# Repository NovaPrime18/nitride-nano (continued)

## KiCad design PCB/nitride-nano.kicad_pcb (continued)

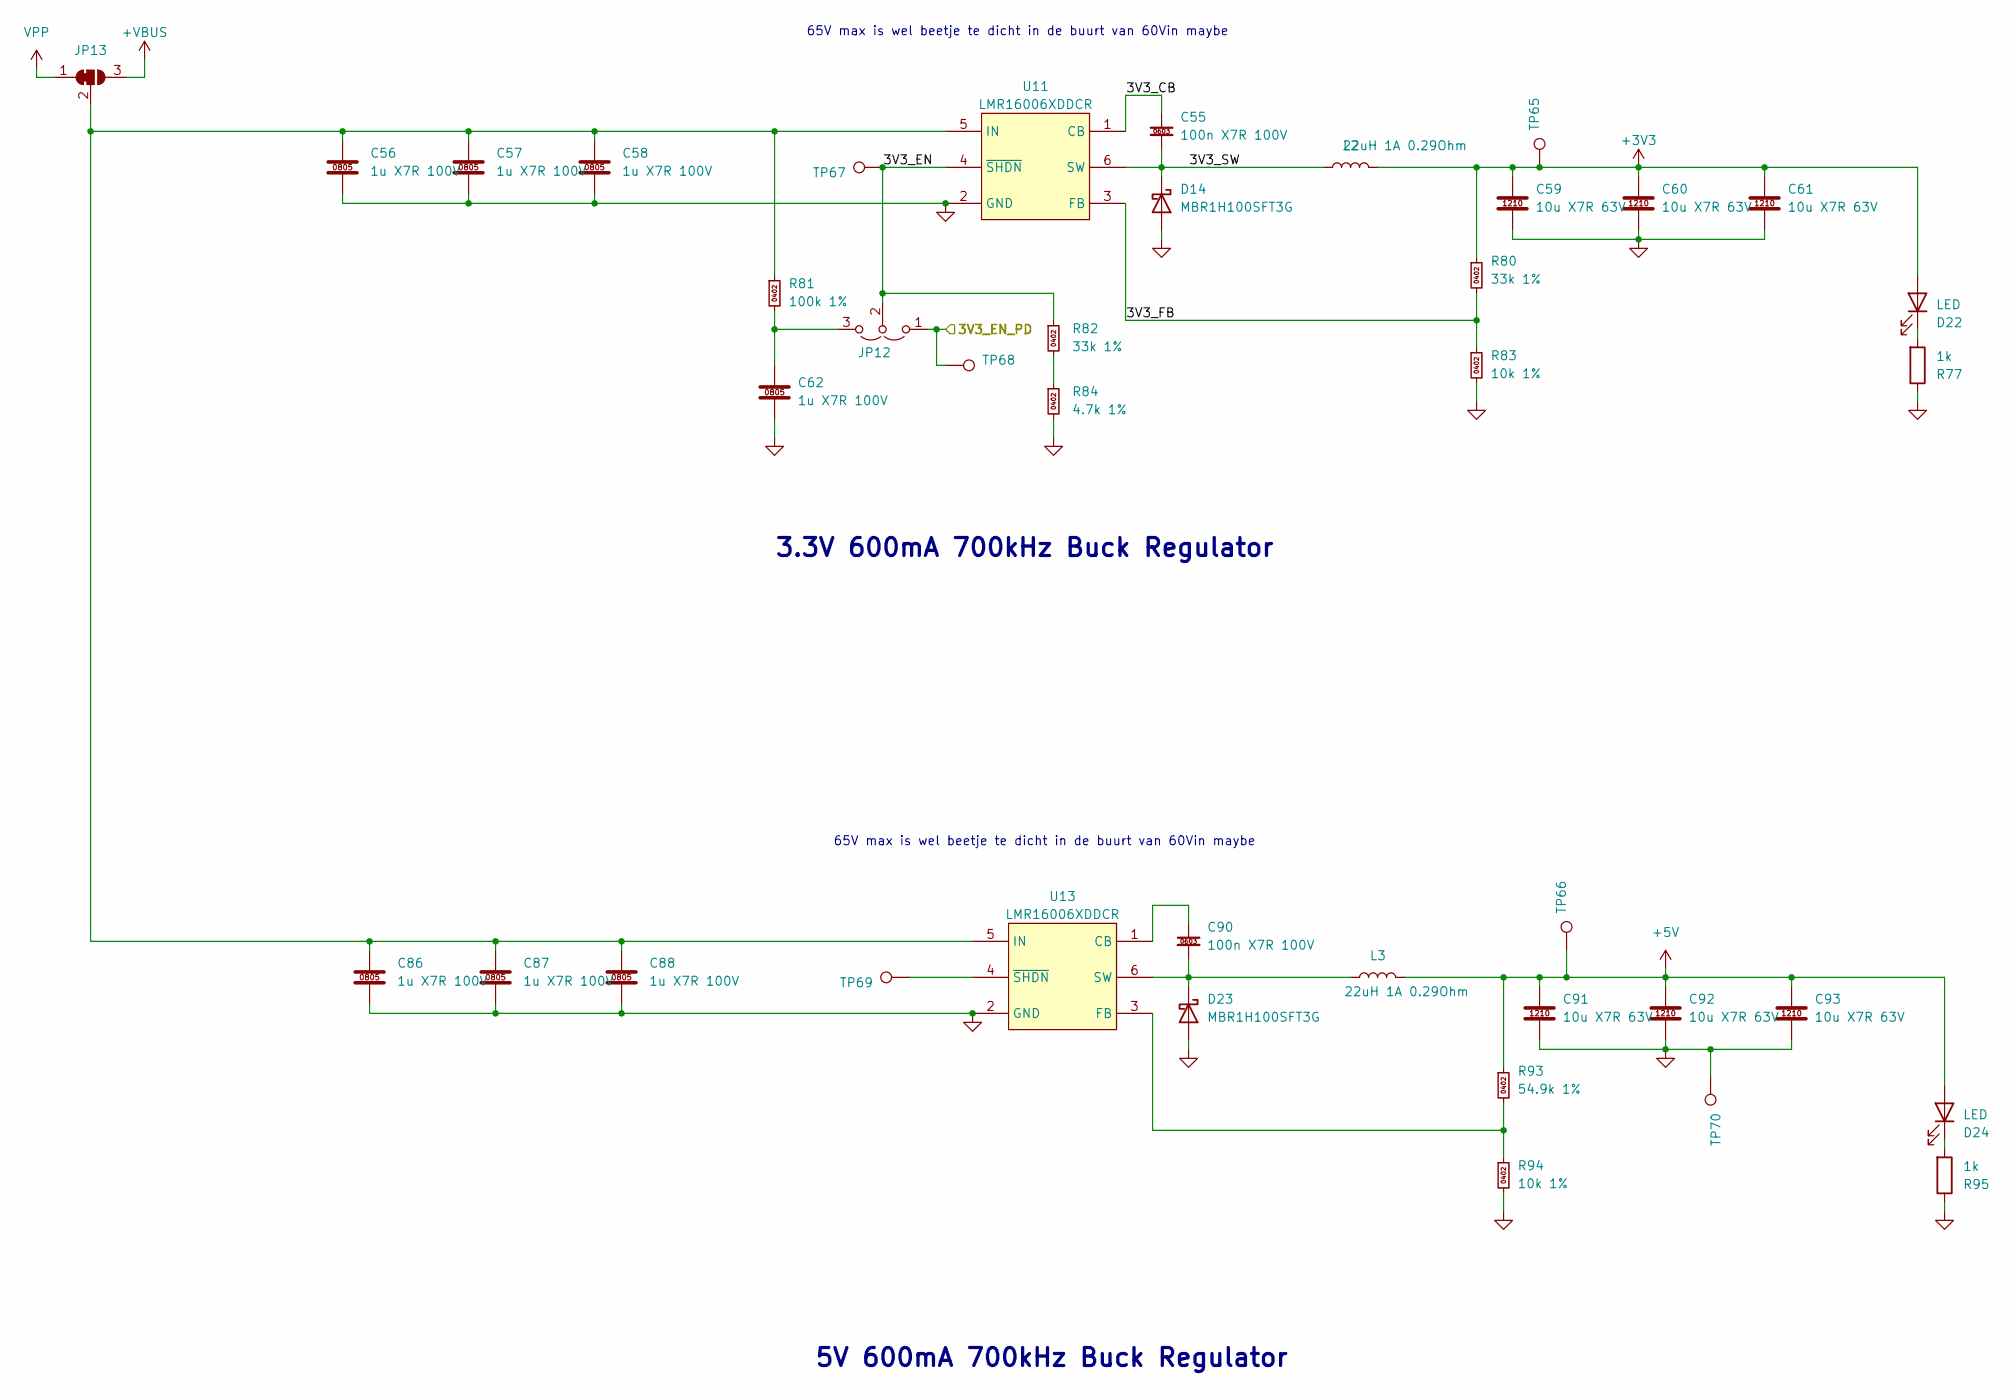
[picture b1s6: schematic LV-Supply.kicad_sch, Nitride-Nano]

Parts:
C55, C90: 100n X7R 100V; C_0603_1608Metric; Manufacturer Part Number CL10B104KC8NNNC; LCSC C15725
C56, C57, C58, C62, C86, C87, C88: 1u X7R 100V; C_0805_2012Metric; Manufacturer Part Number CC0805KKX7R0BB105; LCSC C5370002
C59, C60, C61, C91, C92, C93: 10u X7R 63V; C_1210_3225Metric; Manufacturer Part Number GRM32ER71J106KA12L; LCSC C437568
D14, D23: MBR1H100SFT3G; sod-123fl_305p_260x160x90_n; Manufacturer Part Number MBR1H100SFT3G; LCSC C235757
D22, D24: LED; LED_0603_1608Metric
JP12: jumper_solder_3pad_no; jumper_solder_3pad_no_40x40_20
JP13: SolderJumper_3_Bridged12; SolderJumper-3_P1.3mm_Bridged12_RoundedPad1.0x1.5mm_NumberL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
L2, L3: 22uH 1A 0.29Ohm; SWPA4030S220MT; Manufacturer Part Number SWPA4030S220MT; LCSC C83472
R77, R95: 1k; R_0402_1005Metric
R80, R82: 33k 1%; R_0402_1005Metric; Manufacturer Part Number RC0402FR-0733KL; LCSC C138003
R81: 100k 1%; R_0402_1005Metric; Manufacturer Part Number 0402WGF1003TCE; LCSC C25741
R83, R94: 10k 1%; R_0402_1005Metric; Manufacturer Part Number 0402WGF1002TCE; LCSC C25744
R84: 4.7k 1%; R_0402_1005Metric; Manufacturer Part Number 0402WGF1003TCE; LCSC C25741
R93: 54.9k 1%; R_0402_1005Metric
TP65, TP66, TP67, TP68, TP69, TP70: tp_round_70; TestPoint_Pad_D1.0mm
U11, U13: LMR16006XDDCR; sot6_p95_290x180x110_n; Manufacturer Part Number LMR16006XDDCR; LCSC C87080

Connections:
+3V3: C59.1, C60.1, C61.1, D22.2 (A), L2.2, R80.1, TP65.1 (1_1); also elsewhere on the board
+5V: C91.1, C92.1, C93.1, D24.2 (A), L3.2, R93.1, TP66.1 (1_1); also elsewhere on the board
+VBUS: JP13.3 (B); also elsewhere on the board
/LV-Supply/3V3_CB: C55.1, U11.1 (CB)
/LV-Supply/3V3_EN: JP12.2 (C), R82.1, TP67.1 (1_1), U11.4 (~SHDN); also elsewhere on the board
/LV-Supply/3V3_EN_PD: JP12.1 (A), TP68.1 (1_1); also elsewhere on the board
/LV-Supply/3V3_SW: C55.2, D14.1 (K), L2.1, U11.6 (SW)
unnamed: D22.1 (K), R77.2
unnamed: C90.2, D23.1 (K), L3.1, U13.6 (SW)
unnamed: D24.1 (K), R95.2
unnamed: R82.2, R84.1
unnamed: C90.1, U13.1 (CB)
unnamed: TP69.1 (1_1), U13.4 (~SHDN)
VPP: JP13.1 (A); also elsewhere on the board

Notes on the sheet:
65V max is wel beetje te dicht in de buurt van 60Vin maybe
3.3V 600mA 700kHz Buck Regulator
5V 600mA 700kHz Buck Regulator

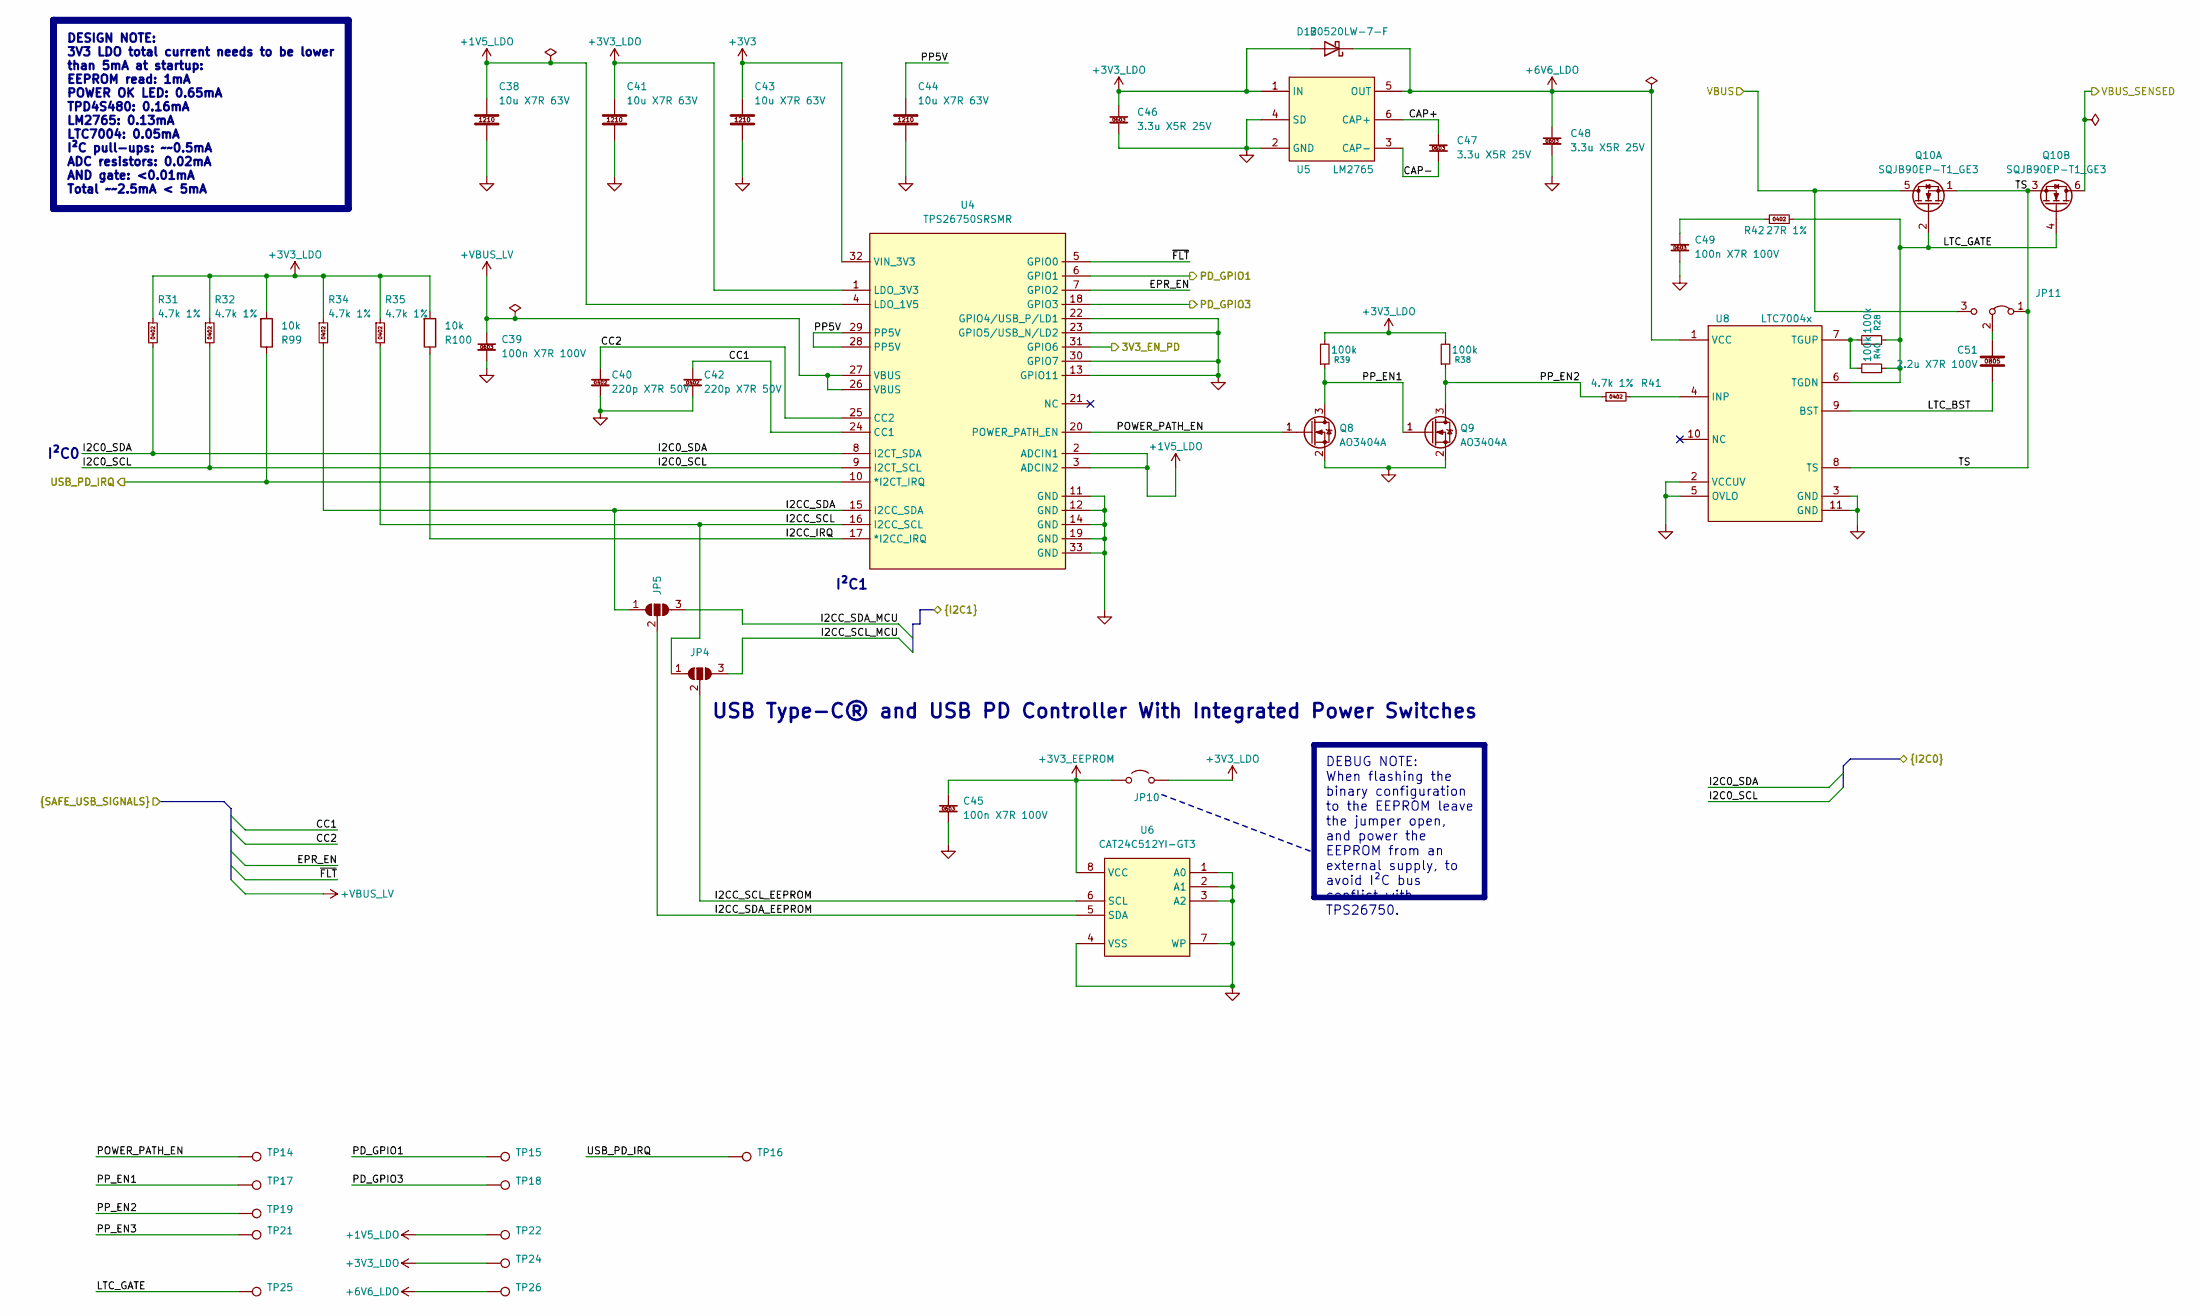
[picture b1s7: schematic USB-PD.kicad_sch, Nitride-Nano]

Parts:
C38, C41, C43, C44: 10u X7R 63V; C_1210_3225Metric; Manufacturer Part Number GRM32ER71J106KA12L; LCSC C437568
C39, C45, C49: 100n X7R 100V; C_0603_1608Metric; Manufacturer Part Number CL10B104KC8NNNC; LCSC C15725
C40, C42: 220p X7R 50V; C_0402_1005Metric; Manufacturer Part Number CL05B221KB5NNNC; LCSC C296710
C46, C47, C48: 3.3u X5R 25V; C_0603_1608Metric; Manufacturer Part Number TCC0603X5R335M250CT; LCSC C5360803
C51: 2.2u X7R 100V; C_0805_2012Metric; Manufacturer Part Number HHV0805R7225K101NSLJ; LCSC C22367838
D12: B0520LW-7-F; sod-123_270x155135_n; Manufacturer Part Number B0520LW-7-F; LCSC C155367
JP4, JP5: SolderJumper_3_Open; SolderJumper-3_P1.3mm_Open_RoundedPad1.0x1.5mm
JP10: jumper_solder_2pad_no_kicad; SolderJumper-2_P1.3mm_Open_RoundedPad1.0x1.5mm
JP11: jumper_solder_3pad_12nc_kicad; SolderJumper-3_P1.3mm_Bridged2Bar12_RoundedPad1.0x1.5mm
Q8, Q9: AO3404A; sot-23-3L_103p_300x130x110_n; Manufacturer Part Number AO3404A; LCSC C30010
Q10: SQJB90EP-T1_GE3; PowerPAKSO-8_127p_513x615x120_n; Manufacturer Part Number SQJB90EP-T1_GE3; LCSC C727731
R28, R38, R39, R40: 100k; R_0402_1005Metric; LCSC C60491
R31, R32, R34, R35, R41: 4.7k 1%; R_0402_1005Metric; Manufacturer Part Number 0402WGF1003TCE; LCSC C105871
R42: 27R 1%; R_0402_1005Metric; Manufacturer Part Number RC0402FR-0727RL; LCSC C138021
R99, R100: 10k; R_0402_1005Metric; LCSC C2906861
TP14, TP15, TP16, TP17, TP18, TP19, TP21, TP22, TP24, TP25, TP26: tp_round_70; TestPoint_Pad_D1.0mm
U4: TPS26750SRSMR; qfn32_40p_400x400x100_tp_280x280_mfg; Manufacturer Part Number TPS26750SRSMR; LCSC C42166327
U5: LM2765; sot236_p95_290x160x110_n; Manufacturer Part Number LM2765M6X/NOPB; LCSC C140270
U6: CAT24C512YI-GT3; JEDEC_MO-153_AA; Manufacturer Part Number CAT24C512YI-GT3; LCSC C56096
U8: LTC7004x; msop_10p_300x490x110_tp168x188_n; Manufacturer Part Number LTC7004EMSE#TRPBF; LCSC C690106

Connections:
+1V5_LDO: C38.1, TP22.1 (1_1), U4.2 (ADCIN1), U4.3 (ADCIN2), U4.4 (LDO_1V5)
+3V3: C43.1, U4.32 (VIN_3V3); also elsewhere on the board
+3V3_EEPROM: C45.1, JP10.1 (A), U6.8 (VCC)
+3V3_LDO: C41.1, C46.1, D12.2 (A), JP10.2 (B), R31.1, R32.1, R34.1, R35.1, R38.2, R39.2, R99.2, R100.2, TP24.1 (1_1), U4.1 (LDO_3V3), U5.1 (IN); also elsewhere on the board
+6V6_LDO: C48.1, D12.1 (K), TP26.1 (1_1), U5.5 (OUT), U8.1 (VCC)
+VBUS: JP11.3 (B), Q10.5 (D); also elsewhere on the board
+VBUS_LV: C39.1, U4.26 (VBUS), U4.27 (VBUS); also elsewhere on the board
/LV-Supply/3V3_EN_PD: U4.31 (GPIO6); also elsewhere on the board
/MCU/I2C0_SCL: R32.2, U4.9 (I2CT_SCL); also elsewhere on the board
/MCU/I2C0_SDA: R31.2, U4.8 (I2CT_SDA); also elsewhere on the board
/MCU/I2CC_SCL_MCU: JP4.3 (B); also elsewhere on the board
/MCU/I2CC_SDA_MCU: JP5.3 (B); also elsewhere on the board
/Power-Sense-In/+VBUS_SENSED: Q10.6 (D); also elsewhere on the board
/USB-PD/CAP+: C47.1, U5.6 (CAP+)
/USB-PD/CAP-: C47.2, U5.3 (CAP-)
/USB-PD/CC1: C42.1, U4.24 (CC1); also elsewhere on the board
/USB-PD/CC2: C40.1, U4.25 (CC2); also elsewhere on the board
/USB-PD/EPR_EN: U4.7 (GPIO2); also elsewhere on the board
/USB-PD/I2CC_IRQ: R100.1, U4.17 (*I2CC_IRQ)
/USB-PD/I2CC_SCL: JP4.1 (A), R35.2, U4.16 (I2CC_SCL)
/USB-PD/I2CC_SCL_EEPROM: JP4.2 (C), U6.6 (SCL)
/USB-PD/I2CC_SDA: JP5.1 (A), R34.2, U4.15 (I2CC_SDA)
/USB-PD/I2CC_SDA_EEPROM: JP5.2 (C), U6.5 (SDA)
/USB-PD/LTC_BST: C51.2, U8.9 (BST)
/USB-PD/LTC_GATE: Q10.2 (G), Q10.4 (G), R28.1, R40.1, R42.2, TP25.1 (1_1), U8.6 (TGDN)
/USB-PD/PD_GPIO1: TP15.1 (1_1), U4.6 (GPIO1); also elsewhere on the board
/USB-PD/PD_GPIO3: TP18.1 (1_1), U4.18 (GPIO3); also elsewhere on the board
/USB-PD/POWER_PATH_EN: Q8.1 (G), TP14.1 (1_1), U4.20 (POWER_PATH_EN)
/USB-PD/PP5V: C44.1, U4.28 (PP5V), U4.29 (PP5V)
/USB-PD/PP_EN1: Q8.3 (D), Q9.1 (G), R39.1, TP17.1 (1_1)
/USB-PD/PP_EN2: Q9.3 (D), R38.1, R41.1, TP19.1 (1_1)
/USB-PD/PP_EN3: TP21.1 (1_1)
/USB-PD/TS: JP11.1 (A), Q10.1 (S), Q10.3 (S), U8.8 (TS)
/USB-PD/USB_PD_IRQ: R99.1, TP16.1 (1_1), U4.10 (*I2CT_IRQ); also elsewhere on the board
/USB-PD/~FLT: U4.5 (GPIO0); also elsewhere on the board
unnamed: C49.1, R42.1
unnamed: C51.1, JP11.2 (C)
unnamed: R41.2, U8.4 (INP)
unnamed: R28.2, R40.2, U8.7 (TGUP)

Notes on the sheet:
USB Type-C® and USB PD Controller With Integrated Power Switches
I²C1
I²C0
DEBUG NOTE: When flashing the binary configuration to the EEPROM leave the jumper open, and power the EEPROM from an external supply, to avoid I²C bus conflict with TPS26750.
DESIGN NOTE: 3V3 LDO total current needs to be lower than 5mA at startup: EEPROM read: 1mA POWER OK LED: 0.65mA TPD4S480: 0.16mA LM2765: 0.13mA LTC7004: 0.05mA I²C pull-ups: ~~0.5mA ADC resistors: 0.02mA AND gate: <0.01mA Total ~~2.5mA < 5mA

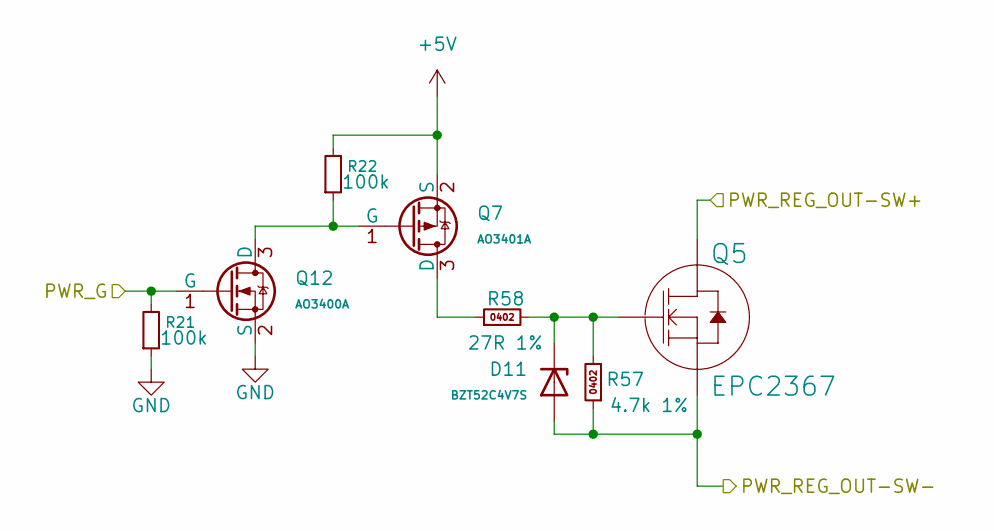
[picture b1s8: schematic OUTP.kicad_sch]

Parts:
D11: BZT52C4V7S; D_SOD-323; Part BZT52C4V7S; LCSC C19077439
Q5: EPC2367; D1068; Part Number EPC2367
Q7: AO3401A; Q_SOT-23; Part AO3401A; LCSC C15127
Q12: AO3400A; Q_SOT-23; Part AO3400A; LCSC C20917
R21, R22: 100k; R_0402_1005Metric
R57: 4.7k 1%; R_0402_1005Metric; Manufacturer Part Number 0402WGF1003TCE; LCSC C105871
R58: 27R 1%; R_0402_1005Metric; Manufacturer Part Number RC0402FR-0727RL; LCSC C138021

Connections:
+5V: Q7.2 (S), R22.2; also elsewhere on the board
/MCU/Turn_on_output: Q12.1 (G), R21.2; also elsewhere on the board
/OUTP-SW/PWR_REG_OUT-SW+: Q5.3 (D), Q5.5 (D); also elsewhere on the board
unnamed: D11.1, Q5.1 (G), R57.2, R58.2
unnamed: Q7.3 (D), R58.1
unnamed: Q7.1 (G), Q12.3 (D), R22.1

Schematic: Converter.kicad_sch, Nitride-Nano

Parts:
C2, C6, C29: 100nF; C_0402_1005Metric; LCSC C162178
C4: 470nF; C_0402_1005Metric; LCSC C7393859
C5: 4.7uF; C_0402_1005Metric; LCSC C23733
C7, C14: 100uF; CP_Elec_10x12.6; Voltage 100V; JLC C3274502
C8, C9, C16, C28: 10uF; C_1210_3225Metric; Voltage 100V; LCSC C5156756
C10, C11, C12, C13, C17, C18, C19, C20, C23, C24, C73: 100nF; C_0402_1005Metric; Voltage 100V; LCSC C162178
C15, C25: 1nF; C_0402_1005Metric; Voltage 50V; LCSC C1523
C21, C22: 1uF; C_0603_1608Metric; Voltage 100V; LCSC C23829972
C26, C27: 100pF; C_0402_1005Metric
C50: 10n X7R 100V; C_0402_1005Metric; Manufacturer Part Number CC0402KRX7R0BB103; LCSC C527014
C85: 100n X7R 100V; C_0603_1608Metric; Manufacturer Part Number CL10B104KC8NNNC; LCSC C15725
D1, D2: BZX58550-C5V1X; D_SOD-523; JLC C3736541
D3, D4: PMEG6020ETP,115; D_SOD-128; LCSC C179434
D5, D6: BAT46WS; D_SOD-323; Forward Voltage (Vf@If) 1V@250mA; Reverse Voltage (Vr) 100V; Part BAT46WS; LCSC C7502692
D20: LED; LED_0603_1608Metric; LCSC C2286
D25, D26, D27, D28: PMEG3005EL,315; D_SOD-882; JLC C282565
FB1, FB2, FB3, FB4, FB5, FB6, FB7, FB8: TBD; L_1210_3225Metric; LCSC C48543473
JP1: SolderJumper_3_Bridged12; SolderJumper-3_P1.3mm_Bridged12_RoundedPad1.0x1.5mm_NumberL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
JP15: Jumper_2_Bridged; SolderJumper-2_P1.3mm_Bridged_RoundedPad1.0x1.5mm
L1: 2.2uH; IND-SMD_L7.5-W7.2-1; JLC C5125746
NT2: nt_2pad_20x20_20_60x20; NetTie-2_SMD_Pad0.5mm
Q1, Q2, Q3, Q4: EPC2367; D1068; Part Number EPC2367
R1: 147k 1%; R_0402_1005Metric; LCSC C64171
R3: 100k; R_0402_1005Metric
R4, R75: 75k; R_0402_1005Metric; LCSC C25798
R5, R7, R19: 357k; R_0402_1005Metric; LCSC C27005
R6: 100k; R_0402_1005Metric; LCSC C60491
R8: 64.9k; R_0402_1005Metric; LCSC C26984
R9: 0.002; R_1206_3216Metric; JLC C46635910
R10: 0; R_0402_1005Metric; JLC C60485
R11, R13: 0; R_0402_1005Metric; LCSC C60485
R12: 0; R_0402_1005Metric; LCSC C25148
R14, R15: 47; R_0402_1005Metric; LCSC C25118
R16: 18k; R_0402_1005Metric; LCSC C25762
R20, R36, R48, R49, R87: 10k; R_0402_1005Metric; LCSC C2906861
R23, R24: 10; R_0402_1005Metric; LCSC C25077
R72: 4.7k 1%; R_0402_1005Metric; Manufacturer Part Number 0402WGF1003TCE; LCSC C105871
R73: 10k @25°C; R_0402_1005Metric; LCSC C77131
R85, R86: 124k; R_0402_1005Metric; LCSC C36777
R101: 1k; R_0402_1005Metric; LCSC C106235
TP32, TP33, TP34: tp_round_70; TestPoint_Pad_D1.0mm
U1: LT8390AIUFD-PBF; UFD_28_ADI; LCSC C673800
U7: TMUX1574RSV; UQFN-16_1.8x2.6mm_P0.4mm; JLC C2673120

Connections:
+3V3: C73.1, R72.1, U7.14 (VDD); also elsewhere on the board
+5V: JP15.1 (A); also elsewhere on the board
/Converter/CC_Set: R48.1; also elsewhere on the board
/Converter/CNV-EN-LOADEN: U1.8 (LOADEN); also elsewhere on the board
/Converter/CV_Set: R36.2; also elsewhere on the board
/Converter/Conv-Disable: R7.2, R8.1, U1.6 (EN/UVLO); also elsewhere on the board
/Converter/High-Gain: U7.15 (SEL); also elsewhere on the board
/Converter/IAMP-In: U7.1 (S1B); also elsewhere on the board
/Converter/IAMP-Ref-In: U7.4 (S2B); also elsewhere on the board
/Converter/INTVCC: C5.1, D5.2, D6.2, JP1.3 (B), JP15.2 (B), R6.1, U1.5 (INTVCC)
/Converter/ISMON: R49.2, U1.13 (ISMON); also elsewhere on the board
/Converter/ISN-L: U1.12 (ISN), U7.5 (D2)
/Converter/ISP-L: U1.11 (ISP), U7.2 (D1)
/Converter/PWR_REG_OUT+: C29.1, FB5.2, FB6.2, FB7.2, FB8.2; also elsewhere on the board
/Converter/PWR_UNREG_IN: C6.1, FB1.1, FB2.1, FB3.1, FB4.1; also elsewhere on the board
/Converter/TEMP_SENSE_CONV: C85.1, R72.2, R73.1; also elsewhere on the board
/Converter/VREF: C4.1, R3.1, R5.1, U1.9 (VREF)
/Converter/Vsense_REG_OUT: R86.2, R87.2; also elsewhere on the board
/Power-Sense-Out/SENSE_N: U7.3 (S2A); also elsewhere on the board
unnamed: C15.1, R16.2
unnamed: C50.1, R101.1
unnamed: C23.2, D1.2 (A), D4.1 (K), Q1.2 (S), Q1.4 (S), Q2.3 (D), Q2.5 (D), R9.1, R14.2, U1.28 (SW1)
unnamed: C23.1, D1.1 (K), R24.2, U1.27 (BST1)
unnamed: C24.2, D2.2 (A), D3.2 (A), L1.2, Q3.3 (D), Q3.5 (D), Q4.2 (S), Q4.4 (S), U1.23 (SW2)
unnamed: C24.1, D2.1 (K), R23.2, U1.24 (BST2)
unnamed: D5.1, R24.1
unnamed: D6.1, R23.1
unnamed: C14.1, C16.1, C17.1, C18.1, C19.1, C20.1, C21.1, C28.1, D3.1 (K), D20.2 (A), FB5.1, FB6.1, FB7.1, FB8.1, Q4.3 (D), Q4.5 (D), R19.1, R85.1, U1.21 (VOUT)
unnamed: D20.1 (K), R75.1
unnamed: D25.2 (A), Q2.1 (G), R11.2
unnamed: D25.1 (K), R11.1, U1.26 (BG1)
unnamed: D26.2 (A), Q1.1 (G), R10.2
unnamed: D26.1 (K), R10.1, U1.1 (TG1)
unnamed: D27.2 (A), Q4.1 (G), R13.2
unnamed: D27.1 (K), R13.1, U1.22 (TG2)
unnamed: D28.2 (A), Q3.1 (G), R12.2
unnamed: D28.1 (K), R12.1, U1.25 (BG2)
unnamed: JP1.1 (A), U1.19 (SYNC/SPRD)
unnamed: L1.1, R9.2, R15.2
unnamed: NT2.1, R73.2
unnamed: R85.2, R86.1
unnamed: R6.2, U1.14 (*PGOOD)
unnamed: R4.1, R5.2, R48.2, U1.10 (CTRL)
unnamed: R19.2, R20.1, R36.1, U1.16 (FB)
unnamed: C25.2, R15.1, U1.3 (LSN)
unnamed: C25.1, R14.1, U1.2 (LSP)
unnamed: R1.1, U1.18 (RT)
unnamed: C2.1, R3.2, U1.15 (SS)
unnamed: U1.17 (VC), U7.7 (D3)
unnamed: C7.1, C8.1, C9.1, C10.1, C11.1, C12.1, C13.1, C22.1, FB1.2, FB2.2, FB3.2, FB4.2, Q1.3 (D), Q1.5 (D), R7.1, U1.4 (VIN)
unnamed: C26.1, R16.1, U7.9 (S3A)
unnamed: C27.1, R101.2, U7.8 (S3B)

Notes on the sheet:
Or Coilcraft: C3911537
1MHz
Was; CMOZ5L1
5A standard limit
36.7V standard output
SSFM Off

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
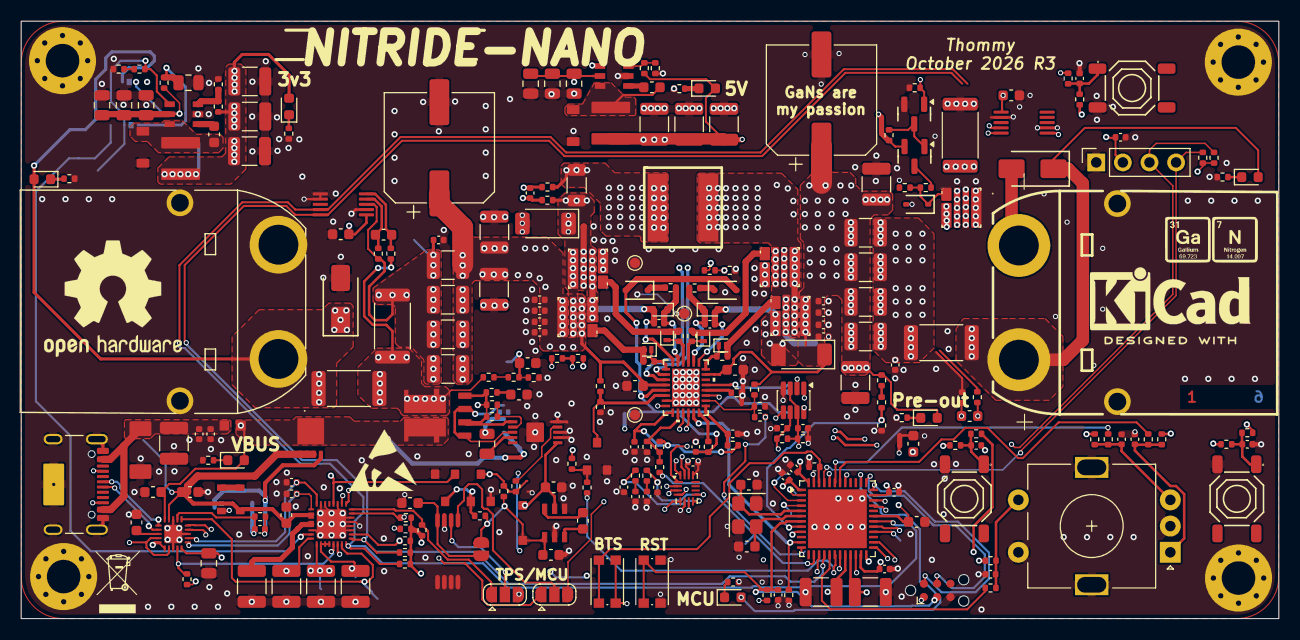
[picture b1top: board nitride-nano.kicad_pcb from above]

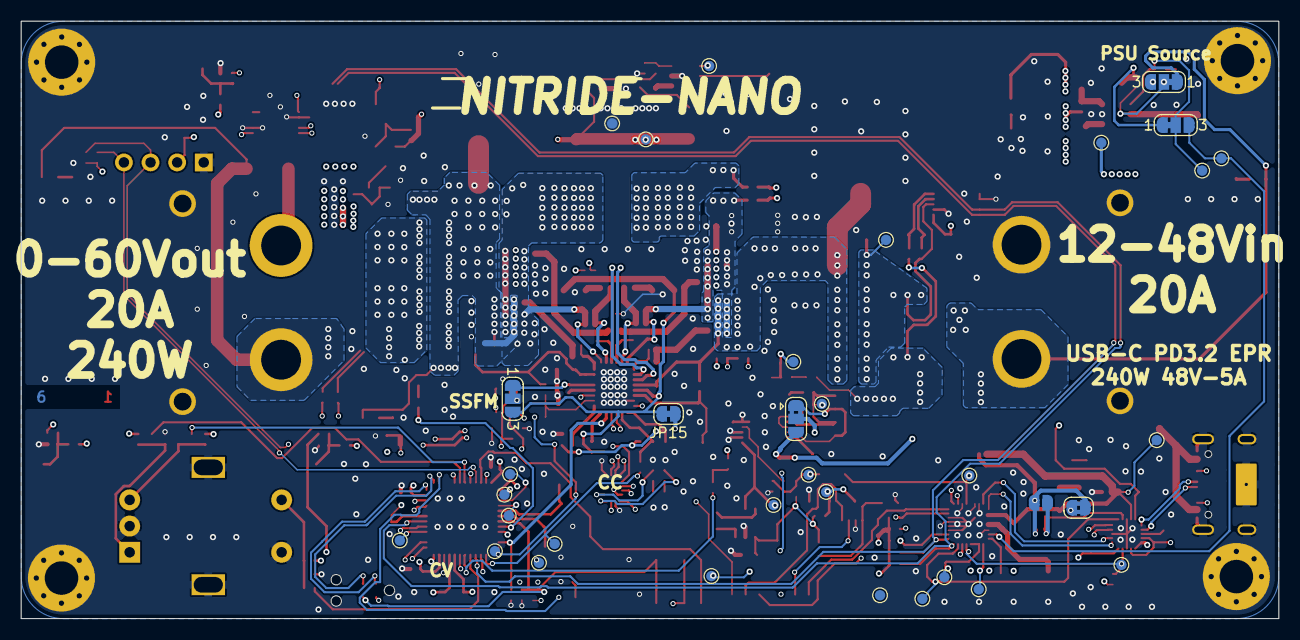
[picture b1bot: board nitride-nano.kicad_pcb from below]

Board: 6 copper layers, 120.0 x 57.0 mm, 303 parts (34 on the bottom side), 157 nets.

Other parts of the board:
JP16: SolderJumper_3_Bridged12; SolderJumper-3_P1.3mm_Bridged12_RoundedPad1.0x1.5mm_NumberL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
R43: 100k; R_0402_1005Metric
R92: 10k; R_0402_1005Metric

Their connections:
/LV-Supply/3V3_EN: JP16.2 (C); also elsewhere on the board
/LV-Supply/3V3_EN_PD: JP16.3 (B); also elsewhere on the board

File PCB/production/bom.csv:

Designator,Footprint,Quantity,Value,LCSC Part #
"C10, C11, C12, C13, C17, C18, C19, C2, C20, C23, C24, C29, C6, C65, C67, C68, C69, C73, C74, C77, C78, C81, C82, C83, C84, C89",0402,26,100nF,C162178
"C14, C7",CP_Elec_10x12.6,2,100uF,C3274502
"C15, C25, C79, C80",0402,4,1nF,C1523
"C16, C28, C66, C70, C8, C9",1210,6,10uF,C5156756
"C21, C22",0603,2,1uF,C23829972
"C26, C27",0402,2,100pF,
"C30, C32, C36, C50",0402,4,10n X7R 100V,C527014
"C31, C56, C57, C58, C62, C86, C87, C88",0805,8,1u X7R 100V,C5370002
"C33, C35, C37, C39, C45, C49, C52, C53, C54, C55, C63, C71, C72, C85, C90",0603,15,100n X7R 100V,C15725
C34,1210,1,4.7u,C913445
"C38, C41, C43, C44, C59, C60, C61, C91, C92, C93",1210,10,10u X7R 63V,C437568
C4,0402,1,470nF,C7393859
"C40, C42",0402,2,220p X7R 50V,C296710
"C46, C47, C48",0603,3,3.3u X5R 25V,C5360803
C5,0402,1,4.7uF,C23733
C51,0805,1,2.2u X7R 100V,C22367838
"C75, C76",0603,2,22pF,C1653
"D1, D2",D_SOD-523,2,BZX58550-C5V1X,C3736541
D11,D_SOD-323,1,BZT52C4V7S,C19077439
D12,sod-123_270x155135_n,1,B0520LW-7-F,C155367
"D14, D23",sod-123fl_305p_260x160x90_n,2,MBR1H100SFT3G,C235757
"D16, D17",D_SMA,2,SMAJ58A,C19077554
"D18, D19, D20, D21, D22, D24, D31",0603,7,LED,C2286
"D25, D26, D27, D28",D_SOD-882,4,"PMEG3005EL,315",C282565
"D3, D4",D_SOD-128,2,"PMEG6020ETP,115",C179434
"D5, D6",D_SOD-323,2,BAT46WS,C7502692
D7,do-214ac_440p_430x250x230_n_p,1,SMAJ48A,C41376401
"D8, D9",sod-323_230p_170x125x100_n,2,BZT52C18SQ,C2857090
"F1, F2",2512,2,20A,C49269483
"FB1, FB2, FB3, FB4, FB5, FB6, FB7, FB8",1210,8,TBD,C48543473
FB9,fer_1608_09_n,1,BLM18SN220TH1D,C710392
J3,CONN-TH_XT90PW-M.G.Y,1,XT-90-M,C3040689
J6,CONN-TH_XT90PW-M,1,XT90-F,C3040690
JP15,SolderJumper-2_P1.3mm_Bridged_RoundedPad1.0x1.5mm,1,Jumper_2_Bridged,
L1,IND-SMD_L7.5-W7.2-1,1,2.2uH,C5125746
"L2, L3",SWPA4030S220MT,2,22uH 1A 0.29Ohm,C83472
P1,USB_C_Receptacle_GCT_USB4105-xx-A_16P_TopMnt_Horizontal,1,USB_C_Plug_USB2.0,C3025063
"Q1, Q2, Q3, Q4, Q5",D1068,5,EPC2367,
Q10,PowerPAKSO-8_127p_513x615x120_n,1,SQJB90EP-T1_GE3,C727731
Q12,Q_SOT-23,1,AO3400A,C20917
"Q13, Q8, Q9",sot-23-3L_103p_300x130x110_n,3,AO3404A,C30010
Q6,vsonp8_65p_330x330x80_mfg,1,AGM612AP,C5349119
Q7,Q_SOT-23,1,AO3401A,C15127
R1,0402,1,147k 1%,C64171
"R10, R11, R13",0402,3,0,C60485
"R100, R20, R30, R33, R36, R48, R49, R53, R61, R62, R63, R64, R67, R69, R71, R74, R87, R88, R89, R90, R91, R92, R94, R97, R99",0402,25,10k,C2906861
"R101, R103, R65, R66, R68, R70, R77, R79, R81, R95",0402,10,1k,C106235
"R102, R42, R52, R54, R58, R83, R98",0402,7,27R 1%,C138021
R12,0402,1,0,C25148
"R14, R15",0402,2,47,C25118
R16,0402,1,18k,C25762
"R19, R5, R59, R7",0402,4,357k,C27005
"R21, R22, R3",0402,3,100k,
"R23, R24, R78",0402,3,10,C25077
"R25, R80, R82",0402,3,33k 1%,C138003
"R28, R38, R39, R40, R43, R44, R46, R47, R6",0402,9,100k,C60491
"R31, R32, R34, R35, R41, R50, R57, R72, R84",0402,9,4.7k 1%,C105871
"R4, R75, R76",0402,3,75k,C25798
"R51, R73",0402,2,10k @25°C,C77131
"R60, R96",2512,2,2mR,C41382683
R8,0402,1,64.9k,C26984
"R85, R86",0402,2,124k,C36777
R9,1206,1,0.002,C46635910
R93,0402,1,54.9k 1%,C11626
"S1, S2, S3",SW-SMD_4P-L5.1-W5.1-P3.70-LS6.5-TL-2,3,"Tactile Button, 160gf",C318884
SW1,RotaryEncoder_Alps_EC11E-Switch_Vertical_H20mm,1,EC11E15244G1,C370970
"SW2, SW3",SW_Push_1P1T_NO_CK_KMR2,2,KMR211NGLFS,C221676
U1,UFD_28_ADI,1,LT8390AIUFD-PBF,C673800
"U11, U13",sot6_p95_290x180x110_n,2,LMR16006XDDCR,C87080
"U12, U9",vssop10_50p_300x300x110_mfg,2,INA228AIDGSR,C2887910
U14,SOT-23-8,1,INA241A1xDDF,
U2,QFN-48-1EP_7x7mm_P0.5mm_EP5.6x5.6mm,1,STM32G474CEUx,C1235412
U3,wqfn20_40p_300x300x80_tp_170x170_n,1,TPD4S480RUKR,C43131250
U4,qfn32_40p_400x400x100_tp_280x280_mfg,1,TPS26750SRSMR,C42166327
U5,sot236_p95_290x160x110_n,1,LM2765,C140270
U6,JEDEC_MO-153_AA,1,CAT24C512YI-GT3,C56096
U7,UQFN-16_1.8x2.6mm_P0.4mm,1,TMUX1574RSV,C2673120
U8,msop_10p_300x490x110_tp168x188_n,1,LTC7004x,C690106
Y1,Crystal_SMD_3225-4Pin_3.2x2.5mm,1,8M,C2682775

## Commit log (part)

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2026-05-07 Fixed the library again
2026-05-07 Cleaned up the hierarchy
2026-05-08 inductor, output fets
2026-05-09 Starting with layout, oled, encoder, xt90
2026-05-15 Finished layout
2026-05-19 Started routing
2026-05-19 Testtest
2026-05-21 Finished routing
2026-05-21 removed lic
2026-05-21 added Cern licensce
2026-05-21 Enhance README with detailed project information
    Expanded the README with detailed specifications, hardware components, firmware features, and acknowledgements.
2026-05-21 20A fuse
2026-05-24 fixed pinout of cpu, added freecad file for the housing
2026-05-24 First housing revision
2026-05-25 Added 5V fan psu
2026-05-25 added pics
2026-05-25 del screenshots
2026-05-25 sync
2026-05-27 Ordered Revision
2026-05-31 Improved housing
2026-06-06 changed mistakes on board, first firmware version
2026-06-08 first working firmware
2026-06-10 New UI
2026-06-11 Working EEPROM flasher script
2026-06-12 feat(ssd1306_ui): add power-on delay for SSD1306 display initialization
2026-06-13 Changed UI around a bit, and improved CV handling
2026-06-13 reshuffeld folders
2026-06-13 new pic
2026-06-17 cleanup of pics
2026-06-17 update readme 2
2026-06-27 temp sense works
